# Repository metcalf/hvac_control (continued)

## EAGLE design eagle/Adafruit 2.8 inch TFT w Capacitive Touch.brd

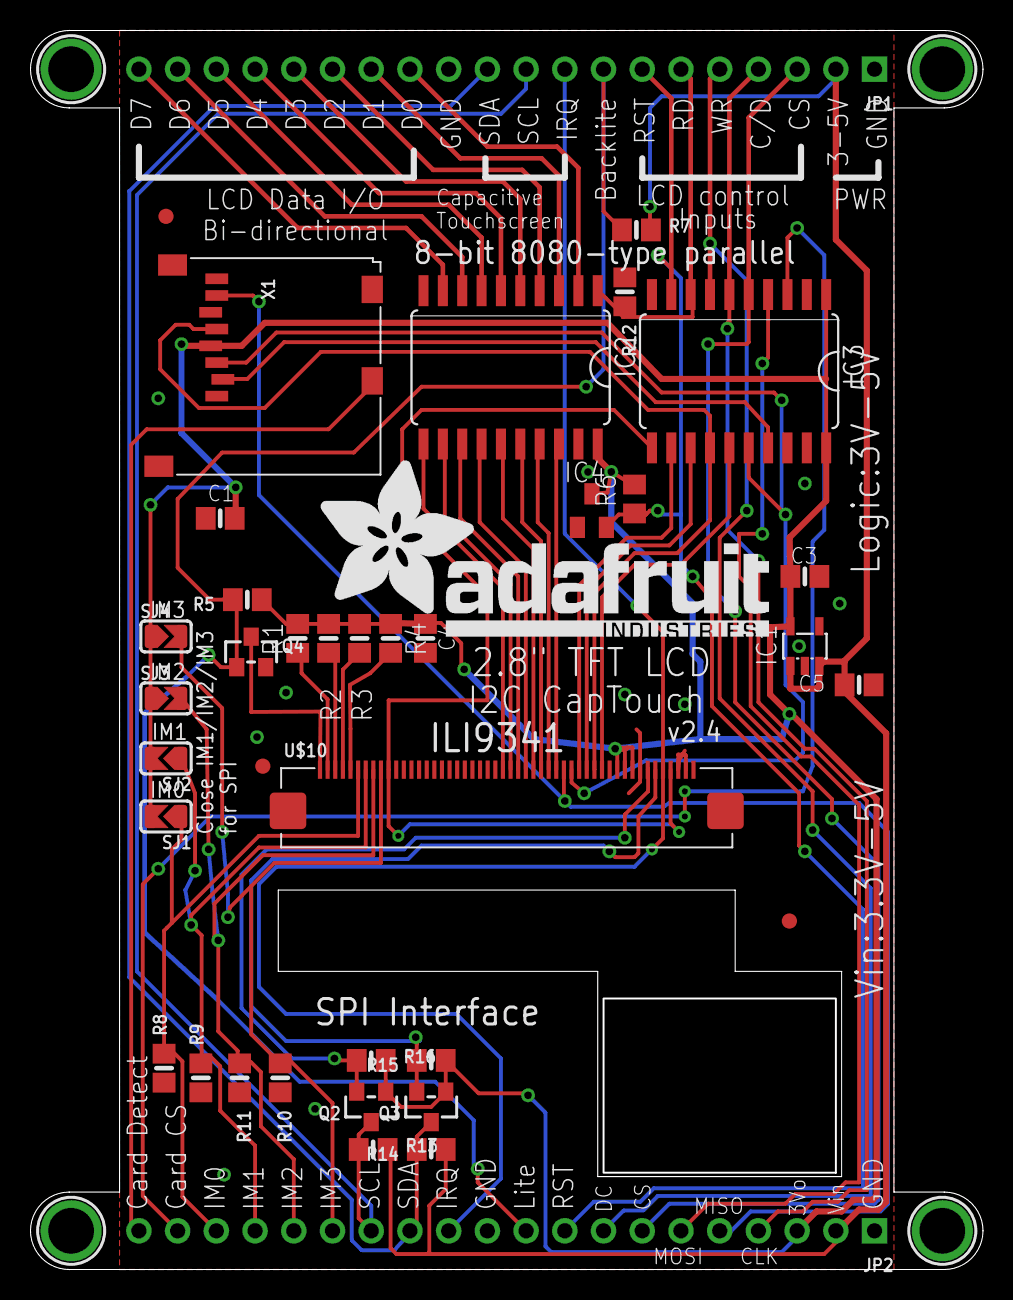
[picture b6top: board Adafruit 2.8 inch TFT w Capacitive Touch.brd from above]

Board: 2 copper layers, 62.5 x 81.3 mm, 43 parts (1 on the bottom side), 50 nets.

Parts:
C1, C3, C4, C5: 10uF; 0805-NO
IC1: MIC5225-3.3; SOT23-5L
IC2, IC3: 74LVC245; SO20W
IC4: APX803-SAG; SOT23
JP1, JP2: 1X20_ROUND
Q2, Q3, Q4: BSS138; SOT23-WIDE
R1, R2, R3, R4: 10; 0805-NO
R5: 2.2K; 0805-NO
R6: 10K; R0805
R7: 1K; 0805-NO
R8, R9, R10, R11, R12, R13, R14, R15, R16: 10K; 0805-NO
SJ1, SJ2, SJ3, SJ4: SOLDERJUMPER_ARROW_NOPASTE
U$7, U$15, U$16, U$17: MOUNTINGHOLE3.0THIN; MOUNTINGHOLE_3.0_PLATEDTHIN
U$9, U$11, U$23: FIDUCIAL; FIDUCIAL_1MM
U$10: 2.8" CTP ILI9341; TFT_2.83IN_240X320_50PIN
U$19: ADAFRUIT_TEXT_30MM
X1: microSD; MICROSD

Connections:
+5V: C5.1, IC1.1, IC1.3, JP1.2, JP2.2, R7.2, R13.2, R14.1
CARDDET: JP2.20, X1.CD2
CTP_IRQ: JP1.9, JP2.12, U$10.46
GND: C1.2, C3.2, C4.2, C5.2, IC1.2, IC2.10, IC2.19, IC3.10, IC3.19, IC4.1, JP1.1, JP1.12, JP2.1, JP2.11, Q4.2, R8.1, R9.1, R10.2, R11.2, R12.1, U$10.43, U$10.48, U$10.49, U$10.50, X1.6, X1.MT1, X1.MT2
IM0: JP2.18, R8.2, SJ1.1, U$10.6
IM1: JP2.17, R9.2, SJ2.1, U$10.7
IM2: JP2.16, R11.1, SJ3.2, U$10.8
IM3: JP2.15, R10.1, SJ4.2, U$10.9
LCD_CS: IC3.15, U$10.38
LCD_CS_5V: IC3.5, JP1.3, JP2.7
LCD_DATA0: IC2.18, U$10.32
LCD_DATA0_5V: IC2.2, JP1.13
LCD_DATA1: IC2.17, U$10.31
LCD_DATA1_5V: IC2.3, JP1.14
LCD_DATA2: IC2.16, U$10.30
LCD_DATA2_5V: IC2.4, JP1.15
LCD_DATA3: IC2.15, U$10.29
LCD_DATA3_5V: IC2.5, JP1.16
LCD_DATA4: IC2.14, U$10.28
LCD_DATA4_5V: IC2.6, JP1.17
LCD_DATA5: IC2.13, U$10.27
LCD_DATA5_5V: IC2.7, JP1.18
LCD_DATA6: IC2.12, U$10.26
LCD_DATA6_5V: IC2.8, JP1.19
LCD_DATA7: IC2.11, U$10.25
LCD_DATA7_5V: IC2.9, JP1.20
LCD_LITE: JP1.8, JP2.10, Q4.1, R5.2, R7.1
LCD_RD: IC3.12, U$10.35
LCD_RD_5V: IC2.1, IC3.8, JP1.6, R12.2
LCD_RS: IC3.14, U$10.37, X1.5
LCD_RST: IC3.11, U$10.10, U$10.47
LCD_RST_5V: IC3.9, IC4.2, JP1.7, JP2.9, R6.1
LCD_RS_5V: IC3.6, JP1.4, JP2.4
LCD_WR: IC3.13, U$10.36
LCD_WR_5V: IC3.7, JP1.5, JP2.8
unnamed: R4.2, U$10.5
unnamed: R1.2, U$10.2
unnamed: R2.2, U$10.3
unnamed: R3.2, U$10.4
unnamed: Q4.3, U$10.1
SCL_3V: Q2.2, R16.1, U$10.44
SCL_5V: JP1.10, JP2.14, Q2.3, R13.1
SDA_3V: Q3.2, R15.2, U$10.45
SDA_5V: JP1.11, JP2.13, Q3.3, R14.2
SDI_3V: IC3.16, U$10.34, X1.3
SDI_5V: IC3.4, JP2.6
SDO: JP2.5, U$10.33, X1.7
SD_CS_3V: IC3.17, X1.2
SD_CS_5V: IC3.3, JP2.19
VCC: C1.1, C3.1, C4.1, IC1.5, IC2.20, IC3.1, IC3.20, IC4.3, JP2.3, Q2.1, Q3.1, R1.1, R2.1, R3.1, R4.1, R5.1, R6.2, R15.1, R16.2, SJ1.2, SJ2.2, SJ3.1, SJ4.1, U$10.40, U$10.41, U$10.42, X1.4

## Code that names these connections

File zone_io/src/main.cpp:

#include <stdint.h>
#include <string.h>

#include <avr/interrupt.h>
#include <avr/io.h>
#include <avr/wdt.h>
#include <util/delay.h>

#define VLV_SW_CLK F_CLK_PER / 2
#define UART_BAUD 9600
#define SEND_INTERVAL_MS 450

struct Bits {
    unsigned b0 : 1, b1 : 1, b2 : 1, b3 : 1, b4 : 1, b5 : 1, b6 : 1, b7 : 1;
};
union BitByte {
    struct Bits bits;
    unsigned char byte;
};

volatile uint16_t vlv_sw_period_;

uint8_t port_states_[3];
volatile uint8_t tx_pos_;
BitByte tx_buffer_[3] = {(0x00 << 6), (0x01 << 6), (0x02 << 6)};

uint8_t getVlvState() {
    uint8_t vlv_sw_freq = VLV_SW_CLK / vlv_sw_period_;
    // NB: Rectified AC is double mains frequency (120hz)
    if (vlv_sw_freq < 30) {
        return 0; // Assume off
    } else if (vlv_sw_freq < 90) {
        return 1; // Assume one channel on (~60hz)
    } else {
        return 2; // Assume both channels on (~120hz)
    }
}

void setupUSART() {
    VPORTA.DIR |= PIN1_bm; // TxD on PA1
    USART1.CTRLA = USART_DREIE_bm;
    USART1.CTRLB = USART_TXEN_bm; // TX only
    USART1.BAUD = (uint16_t)((float)(F_CLK_PER * 64 / (16 * (float)UART_BAUD)) + 0.5);
    // Configure async 8N1 (this is the default anyway, being explicit for clarity)
    USART1.CTRLC = USART_CMODE_ASYNCHRONOUS_gc | USART_PMODE_DISABLED_gc | USART_SBMODE_1BIT_gc |
                   USART_CHSIZE_8BIT_gc;
}

void txNext() {
    USART1_TXDATAL = tx_buffer_[tx_pos_].byte;
    tx_pos_ = (tx_pos_ + 1) % sizeof(tx_buffer_);
}

void startTx() {
    if (tx_pos_ != 0 || (USART1.STATUS & USART_DREIF_bm)) {
        return; // We're still writing, skip this Tx
    }

    BitByte vlv_state = {.byte = getVlvState()};

    tx_buffer_[0] = {.bits = {.b0 = VPORTA.IN & PIN2_bm, // FC1_V
                              .b1 = VPORTA.IN & PIN3_bm, // FC1_OB
                              .b2 = VPORTA.IN & PIN4_bm, // FC2_V
                              .b3 = VPORTA.IN & PIN5_bm, // FC2_OB
                              .b4 = VPORTA.IN & PIN6_bm, // FC3_V
                              .b5 = VPORTA.IN & PIN7_bm, // FC3_OB
                              .b6 = 0,
                              .b7 = 0}};
    tx_buffer_[1] = {.bits = {.b0 = VPORTB.IN & PIN5_bm, // FC4_V
                              .b1 = VPORTB.IN & PIN4_bm, // FC4_OB
                              .b2 = VPORTB.IN & PIN1_bm, // TS1_W
                              .b3 = VPORTB.IN & PIN2_bm, // TS1_Y
                              .b4 = VPORTB.IN & PIN3_bm, // TS2_W
                              .b5 = VPORTB.IN & PIN0_bm, // TS2_Y
                              .b6 = 1,
                              .b7 = 0}};
    tx_buffer_[2] = {.bits = {.b0 = VPORTC.IN & PIN1_bm, // TS3_W
                              .b1 = VPORTC.IN & PIN2_bm, // TS3_Y
                              .b2 = VPORTC.IN & PIN3_bm, // TS4_W
                              .b3 = 0,                   // TS4_Y (not connected)
                              .b4 = vlv_state.bits.b0,
                              .b5 = vlv_state.bits.b1,
                              .b6 = 0,
                              .b7 = 1}};

    txNext();
}

void setupPins() {
    PORTA.PIN2CTRL |= PORT_PULLUPEN_bm; // FC1_V
    PORTA.PIN3CTRL |= PORT_PULLUPEN_bm; // FC1_OB
    PORTA.PIN4CTRL |= PORT_PULLUPEN_bm; // FC2_V
    PORTA.PIN5CTRL |= PORT_PULLUPEN_bm; // FC2_OB
    PORTA.PIN6CTRL |= PORT_PULLUPEN_bm; // FC3_V
    PORTA.PIN7CTRL |= PORT_PULLUPEN_bm; // FC3_OB
    PORTB.PIN1CTRL |= PORT_PULLUPEN_bm; // TS1_W
    PORTB.PIN2CTRL |= PORT_PULLUPEN_bm; // TS1_Y
    PORTB.PIN3CTRL |= PORT_PULLUPEN_bm; // TS2_W
    PORTB.PIN5CTRL |= PORT_PULLUPEN_bm; // FC4_V
    PORTB.PIN4CTRL |= PORT_PULLUPEN_bm; // FC4_OB
    PORTB.PIN0CTRL |= PORT_PULLUPEN_bm; // TS2_Y
    PORTC.PIN0CTRL |= PORT_PULLUPEN_bm; // TS3_W
    PORTC.PIN1CTRL |= PORT_PULLUPEN_bm; // TS3_W
    PORTC.PIN2CTRL |= PORT_PULLUPEN_bm; // TS3_Y
}

void setupVlvTimer() {
    // Configure TCB0 on WO0/PC0 for frequency measurement for VLV_SW_IO
    PORTMUX.TCBROUTEA = PORTMUX_TCB0_ALT1_gc;
    TCB0.CTRLB = TCB_CNTMODE_FRQ_gc; // Frequency count mode
    //TCB0.EVCTRL = TCB_CAPTEI_bm; // I had this set originally but think it isn't necessary?
    TCB0.INTCTRL = TCB_CAPT_bm;
    TCB0.CTRLA =
        (TCB_ENABLE_bm | TCB_CLKSEL_DIV2_gc); // Configure tach frequency measurement @ ~156khz
}

int main(void) {
    wdt_enable(WDTO_1S);

    CLKCTRL.MCLKCTRLB = CLKCTRL_PEN_bm | CLKCTRL_PDIV_64X_gc; // Divide main clock by 64 = 312500hz

    setupUSART();
    setupPins();
    setupVlvTimer();

    while (1) {
        wdt_reset();

        // Poll pin states every 833us for 50ms. This gives us a sample rate
        // of 1200hz on a 120hz signal for 6 cycles
        memset(port_states_, 0, sizeof(port_states_));
        for (int i = 0; i < 60; i++) {
            // Exclude PA0(UDPI) and PA1(UART)
            port_states_[0] |= VPORTA.IN & ~(PIN0_bm | PIN1_bm);
            port_states_[1] |= VPORTB.IN;
            // Exclude PC0 (VLV_SW)
            port_states_[2] |= VPORTC.IN & ~(PIN0_bm);

            _delay_us(833);
        }

        startTx();

        // Delay while sending since we don't need the data very frequently
        wdt_reset();
        _delay_ms(SEND_INTERVAL_MS);
    }
}

ISR(TCB0_INT_vect) {
    if (TCB0.INTFLAGS & TCB_OVF_bm) {
        // If we overflowed, clear the overflow bit and set an invalid period
        TCB0.INTFLAGS &= ~TCB_OVF_bm;
        vlv_sw_period_ = 0;
    } else {
        vlv_sw_period_ = TCB0.CCMP; // reading CCMP clears interrupt flag
    }
}

ISR(USART1_DRE_vect) {
    if (tx_pos_ == 0) {
        return; // Nothing to write right now
    }

    txNext();
}

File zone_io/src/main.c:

#include <stdint.h>
#include <string.h>

#include "avr/interrupt.h"
#include "avr/io.h"
#include "avr/wdt.h"
#include "util/atomic.h"
#include "util/delay.h"

#define VLV_SW_CLK F_CLK_PER / 2
#define UART_BAUD 9600
#define SEND_INTERVAL_MS 450

// Poll 200 times at 1200hz. Gives us 20 full cycles of data and takes ~167ms
// Our read strategy is designed to filter out external noise at the optoisolator inputs.
// The Taco valves in particular throw off a lot of noise and cause pins to flicker.
#define N_SAMPLES 200
// The optoisolators are pretty sensitive so it should read high
// most of the time if the pin is high. The internal pull-ups is very weak (~35kohm)
// so a tiny amount of current (<0.1mA) should pull the pin high. This corresponds to
// something like 0.2mA at the opto input which requires 5-6V.
#define INPUT_THRESHOLD (N_SAMPLES / 4)
// We can set a very low threshold for the one channel state since there should be
// *nothing* on the pin when no channels are on. This also helps avoid rapid switching
// of the pump if the controller thinks the only active channel is rapidly turning on and off.
// We're stuck using a somewhat higher threshold for the both channels state since it has
// to be larger than half the total samples or we could falsely trigger it when only one channel is on.
#define ONE_VALVE_THRESHOLD (N_SAMPLES / 8)
#define BOTH_VALVE_THRESHOLD (uint8_t)(N_SAMPLES * 0.53)

volatile uint16_t vlv12_sw_period_, vlv34_sw_period_;
volatile uint8_t port_read_flag_;
volatile uint8_t port_in_values_[3];
volatile uint8_t *ports_[] = {&VPORTA.IN, &VPORTB.IN, &VPORTC.IN};

volatile uint8_t tx_pos_;
char tx_buffer_[3];

const uint8_t tx_map_[3][6] = {
    {
        // PORTA
        PIN2_bm, // FC1_V
        PIN3_bm, // FC1_OBpwm
        PIN4_bm, // FC2_V
        PIN5_bm, // FC2_OB
        PIN6_bm, // FC3_V
        PIN7_bm, // FC3_OB
    },
    {
        // PORTB
        PIN5_bm, // FC4_V
        PIN4_bm, // FC4_OB
        PIN1_bm, // TS1_W
        PIN2_bm, // TS1_Y
        PIN3_bm, // TS2_W
        PIN0_bm, // TS2_Y
    },
    {
        // PORTC
        PIN0_bm, // TS3_W
        PIN1_bm, // TS4_W
    },
};

void setupUSART() {
    VPORTA.DIR |= PIN1_bm; // TxD on PA1
    // Configure async 8N1 (this is the default anyway, being explicit for clarity)
    USART1.CTRLC = USART_CMODE_ASYNCHRONOUS_gc | USART_PMODE_DISABLED_gc | USART_SBMODE_1BIT_gc |
                   USART_CHSIZE_8BIT_gc;
    USART1.BAUD = (uint16_t)((double)(F_CLK_PER * 64 / (16 * (double)UART_BAUD)) + 0.5);
    USART1.CTRLB = USART_TXEN_bm; // TX only
}

void startTx(uint8_t *port_states, uint8_t vlv12_state, uint8_t vlv34_state) {
    if (USART1.CTRLA & USART_DREIE_bm) {
        return; // We're still writing, skip this Tx
    }

    for (int i = 0; i < 3; i++) {
        int lim = i < 2 ? 6 : 2;
        tx_buffer_[i] = i << 6; // Set payload ID in last 2 bits
        for (int j = 0; j < lim; j++) {
            if (port_states[i] & tx_map_[i][j]) {
                tx_buffer_[i] |= (0x01 << j);
            }
        }
    }

    tx_buffer_[2] |= (vlv12_state << 2) | (vlv34_state << 4);

    USART1.CTRLA |= USART_DREIE_bm;
}

void setupInputPins() {
    VPORTA.DIR = 0;
    VPORTB.DIR = 0;
    VPORTC.DIR = 0;

    register8_t *pins[] = {
        &PORTA.PIN2CTRL, &PORTA.PIN3CTRL, &PORTA.PIN4CTRL, &PORTA.PIN5CTRL,
        &PORTA.PIN6CTRL, &PORTA.PIN7CTRL,

        &PORTB.PIN0CTRL, &PORTB.PIN1CTRL, &PORTB.PIN2CTRL, &PORTB.PIN3CTRL,
        &PORTB.PIN4CTRL, &PORTB.PIN5CTRL,

        &PORTC.PIN0CTRL, &PORTC.PIN1CTRL, &PORTC.PIN2CTRL, &PORTC.PIN3CTRL,
    };

    for (int i = 0; i < (sizeof(pins) / sizeof(pins[0])); i++) {
        // Enable pullups on all input pins and invert inputs since NPN optos pull down
        *pins[i] = (PORT_PULLUPEN_bm | PORT_INVEN_bm);
    }
}

void setupPinCheckTimer() {
    // Sample at 1200hz (10x rectified mains frequency)
    TCA0.SINGLE.PER = (F_CLK_PER + 600) / 1200;
    TCA0.SINGLE.INTCTRL = TCA_SINGLE_OVF_bm;
    TCA0.SINGLE.CTRLA = TCA_SINGLE_CLKSEL_DIV1_gc;
}

int main(void) {
    wdt_enable(0x8); // 1 second (note the constants in avr/wdt are wrong for this chip)

    CPU_CCP = CCP_IOREG_gc; /* Enable writing to protected register MCLKCTRLB */
    CLKCTRL.MCLKCTRLB = CLKCTRL_PEN_bm | CLKCTRL_PDIV_16X_gc; // Divide main clock by 16 = 1.25mhz

    setupInputPins();
    setupUSART();
    setupPinCheckTimer();

    sei(); // Enable interrupts

    while (1) {
        wdt_reset();

        uint8_t port_counts[3][8] = {};

        port_read_flag_ = 0;
        TCA0.SINGLE.INTFLAGS |= TCA_SINGLE_OVF_bm; // Clear interrupt flag
        TCA0.SINGLE.CNT = 0;                       // Start at zero
        TCA0.SINGLE.CTRLA |= TCA_SINGLE_ENABLE_bm; // Start the timer

        for (int i = 0; i < N_SAMPLES; i++) {
            while (1) {
                uint8_t read;
                ATOMIC_BLOCK(ATOMIC_FORCEON) { read = port_read_flag_; }
                if (read) {
                    break;
                }
            }

            for (uint8_t port_idx = 0; port_idx < 3; port_idx++) {
                for (uint8_t pin = 0; pin < 8; pin++) {
                    if (port_in_values_[port_idx] & (1 << pin)) {
                        port_counts[port_idx][pin]++;
                    }
                }
            }
            ATOMIC_BLOCK(ATOMIC_FORCEON) { port_read_flag_ = 0; }
        }

        TCA0.SINGLE.CTRLA &= ~TCA_SINGLE_ENABLE_bm; // Stop the timer

        uint8_t port_states[3] = {0};

        for (uint8_t port_idx = 0; port_idx < 3; port_idx++) {
            for (uint8_t pin = 0; pin < 8; pin++) {

                if (port_counts[port_idx][pin] > INPUT_THRESHOLD) {
                    port_states[port_idx] |= (1 << pin);
                }
            }
        }

        uint8_t vlv_states[2] = {0};
        for (int i = 0; i < 2; i++) {
            // PC2 and PC3 are used for VLV1/2 and VLV3/4 respectively
            uint8_t count = port_counts[2][i + 2];

            if (count > BOTH_VALVE_THRESHOLD) {
                vlv_states[i] = 2; // Both channels on
            } else if (count > ONE_VALVE_THRESHOLD) {
                vlv_states[i] = 1; // One channel on
            } else {
                vlv_states[i] = 0; // Off
            }
        }

        startTx(port_states, vlv_states[0], vlv_states[1]);

        // Delay while sending since we don't need the data very frequently
        wdt_reset();
        _delay_ms(SEND_INTERVAL_MS);
    }
}

ISR(TCA0_OVF_vect) {
    if (port_read_flag_ == 0) {
        for (int i = 0; i < 3; i++) {
            port_in_values_[i] = *ports_[i];
        }
        port_read_flag_ = 1;
    }

    TCA0.SINGLE.INTFLAGS |= TCA_SINGLE_OVF_bm; // Clear interrupt flag
}

ISR(USART1_DRE_vect) {
    USART1_TXDATAL = tx_buffer_[tx_pos_];
    tx_pos_ = (tx_pos_ + 1) % sizeof(tx_buffer_);

    if (tx_pos_ == 0) {
        // Write complete, disable interrupt
        USART1.CTRLA &= ~USART_DREIE_bm;
    }
}

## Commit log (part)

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2024-02-03 Upgrade to esp-idf 5.x
2024-02-06 controller compiles
2024-02-07 wip controller with ui
2024-02-07 move ControllerApp to library
2024-02-07 Refactor ControllerApp to remove uc deps
2024-02-08 got a running test
2024-02-08 Status logging and testing
2024-02-09 Wifi and tests et al
2024-02-20 Fix hardware interfaces, mem allocation, points
2024-02-21 wrap lv_ access in mutex
2024-02-21 lvgl work
2024-02-21 don't track sdkconfig backups
2024-02-21 Faster rtos tick and don't use CS
2024-02-21 Change sdkconfig for perf
2024-02-22 wip loggers
2024-02-22 squareline
2024-02-22 mostly working ui
2024-02-22 Properly init schedule time rollers
2024-02-24 working fancoil/makeup+tester
2024-02-24 wip settings screens
2024-02-24 WIP settings
2024-02-24 WIP synced temp rollers
2024-02-26 More UI work and tests
2024-02-28 more controller wip
2024-02-29 WIP new sensor implementation
2024-02-29 Import rx8111 RTC linux driver verbatim
2024-02-29 Add clock on homescreen
2024-03-01 New config architecture, co2 calibration, some UI improvements
2024-03-04 Add support for 2nd valve sw input pin
2024-03-18 Moar tests
2024-03-23 Fix sleep wake
2024-03-23 some co2 calibration tweaks
2024-03-25 Tests and fixes for co2 calibration
2024-03-25 Include hardware files
2024-03-25 Remove old eagle files now that we have git history
2024-03-27 RTC and CO2 cal debugging
2024-03-28 Initial zone controller UI
2024-03-28 Initial zone controller UI with shared code extracted
2024-03-28 Copy configs from controller
2024-03-28 Compiling with UI
2024-03-29 compiles
2024-03-29 Maybe working test mode
2024-03-29 WIP zone controller tests
2024-04-04 move mutexes out of MessageManager and into *UIManager
2024-04-06 more testing and fixing
2024-04-06 more tests and todos
2024-04-12 Remove 'Force AC' to simplify broken logic
2024-04-14 Finish removing secondary controller and write more tests
2024-06-24 latest boards and cases
2024-07-08 update boards and labeling
2024-07-10 Bump UI
2024-07-10 Initial pid simulator
2024-07-12 hvac.System
2024-07-12 simple fan cooling
2024-07-17 more wip simulator
2024-07-18 wip integration wrong
2024-07-19 pretty reasonable model
2024-07-27 bit of simulator cleanup
2024-08-22 start work on CXI modbus client
2024-08-22 initial fancoil_tester
2024-08-22 rando
2024-08-24 More work on cxi
2024-08-24 WIP weather fetching
2024-08-26 Add fancoil modbus logic to controller
2024-08-31 first pass at weather client
2024-09-01 WIP separate broan code
2024-09-02 working broan code
2024-09-02 Bump the clock on the S&P code too so we don't hit modbus timeouts as much
2024-09-02 Move shared code for the fresh air clients to a shared lib
2024-09-04 Run AC if coil is already cold
2024-09-09 fresh air control updates
2024-09-10 Simplify PID simulation code
2024-09-11 Split out simulation PIDComponent
2024-09-17 more pid algo simplification
2024-09-17 mostly working demand-based modulo linker issues
2024-09-17 move to right place
2024-09-18 linear implementation with demands
2024-09-18 WIP tests
2024-09-19 tests compile
2024-09-20 passing tests
2024-09-21 PID passes tests
2024-09-22 constrain iDemand further to avoid windup
2024-09-29 todo
2024-09-29 wip release script
2024-10-02 make wifi an IDF component and start work on OTA
2024-10-02 compiling OTA client
2024-11-15 No DHW
2024-11-16 WIP switch to pulling weather from home assistant
2024-11-16 compiling with home assistant client
2024-11-17 Remote logging compiles
2024-11-17 bug fixes
2024-11-17 More minor fixes/improvements
2024-11-21 WIP updates and bug fixes
2024-11-21 working HASS client, temporary retreat on remote logging
2024-11-22 working remote logger, some fixes
2024-11-22 memory
2024-11-23 wifi reconnection, lower stack usage in remote_logger
2024-11-25 Fixed crash on formatting issue
2024-11-26 start moving things from shared_libs to components
2024-11-26 Finish moves from shared_libs to components
2024-11-26 WIP migrate controller to ESP IDF
2024-11-26 more WIP migrate to ESP IDF
2024-11-27 Working local unit tests
2024-11-27 cleanup ESP IDF bits
2024-11-30 NetworkTaskManager; Mostly working HVAC switching limits, failing tests
2024-11-30 Fix tests
2024-12-09 Use sdkconfig.defaults for better config management (controller)
2024-12-09 correctly set ESP IDF monitor defaults
2024-12-09 Some cleanup from the ESP IDF move
2024-12-09 Share log_heap_stats
2024-12-09 Update release.sh for ESP IDF
2024-12-09 more NTM
2024-12-09 UI tweaks and rearrange UI folder
2024-12-09 Fix messages
2024-12-09 tweak default name
2024-12-09 zc fixes
2024-12-10 minor zc fixes
2024-12-10 Reduce log level
2024-12-21 zone_controller ota mark valid
2025-06-11 mostly controller bug and test fixes
2025-06-12 few ui bug fixes
2025-06-13 system power and fresh air ID bugs
2025-06-13 do not allow cancelling precooling until we make the ui better
2025-06-13 Add a test main method to properly read gmock command line args
2025-07-08 spaces instead of tabs in logs
2025-07-09 Fix changing equipment config
2025-07-09 Change how algos are initialized
2025-07-09 Add turn on hysteresis to fan
2025-07-09 Tweak parameters to reduce short cycling more
2025-07-09 adjust for outdoor temp, log fancoil state, integral deadband
2025-07-10 fix bug in windup deadzone
2025-07-10 debug pid
2025-07-10 Tune fan parameters a bit more
2025-07-10 Provide more reasonable tuning for fancoils
2025-07-10 Better logging of state
2025-07-10 fix bug preventing OTA
2025-07-10 try to talk to real heatpump
2025-07-12 use std::size other places to reduce risk of bugs
2025-07-12 System On label
2025-07-12 I think this could hide a bug
2025-07-12 start swapping A/B pins
2025-07-12 Fix IncreasesFanSpeedOverTime and Precooling tests for new parameters
2025-07-12 Implement canceling HVAC change limit
2025-07-12 Put the restart button label on the button
2025-07-13 Bump up makeup air speed
2025-07-16 switch modbus TXD pin and add some logging
2025-07-16 Revert "Update esp-modbus to v1.0.18"
    This version introduces some breaking changes by paying attention to the param_type and
    param_size for the descriptors which I have been setting to zero.
    This reverts commit 6b57b70cb332cc7453fbac6a019fac561a86f53f.
2025-07-16 more logging improvements
2025-07-16 Fix inverted fancoil O/B
2025-07-17 Fix clang-format inheritance
2025-07-17 CXI fancoil debugging
2025-07-17 Don't query fancoil if not used
2025-07-17 log coil temps
2025-07-17 more fancoil debug logging
2025-07-17 correct comments on timers in fresh_air_control
2025-07-17 enable overflow interrupt
2025-07-17 Retry all CXI modbus commands with backoff
2025-07-18 Bit higher threshold for activating AC
2025-07-18 use weather data instead of polling fresh air unit
2025-07-18 Fix display of outdoor temp and allow older temps
2025-07-19 Fix tests for switch to weather API
2025-07-19 Fix precooling messaging and make precooling more aggressive
2025-07-22 Reasons to enumbs
2025-07-22 Log on fan/hvac state changes
2025-07-24 extend precooling
2025-07-24 Don't use A/C with cool outdoor temps
2025-07-24 Rewrite zone_io to reduce sensitivity to electrical noise
2025-07-24 ignore eagle backup files
2025-07-24 WIP debugging new zone_io code
2025-07-24 Working new zone_io and fix some tests
2025-07-24 Do not turn zone pump on until at least one valve is open
2025-09-17 Fix release to use sudo
2025-09-23 Fix test thresholds from 4850289e
2025-09-23 Turn on A/C when outdoor temp exceeds a threshold
2025-09-23 Make various ControllerApp constants public to improve tests
2025-09-30 Switch to https for homeassistant
2025-09-30 Make pressure formatting portable
2025-09-30 reformat ESPOTAClient
2025-09-30 Send temperature correction to SCD40
2025-10-01 Report AQI instead of humidity
2025-10-09 adjust temp offset a bit
2025-10-11 Fix deadlock turning on and off
2025-10-15 tap message to scroll
2025-10-27 temperature sensor board for controllers
2025-10-29 Don't mess with heat pump in test mode
2025-10-29 save temp_board as printed
2025-10-30 get rid of apparently unused 'getValve'
2025-10-30 fix logging bug
2025-10-30 Refactor out ZCApp
2025-10-30 Remove dependencies for testability
2025-10-30 Create AbstractZCUIManager for testability
2025-10-30 Get existing tests working again
2025-10-31 logging comment
2025-10-31 Really fix logging this time
2025-10-31 Rate limit state change on valves/pumps
2025-10-31 Better debouncing on zone_io
2025-10-31 Reduce repetitive logging during rate limiting
2025-10-31 Move UI files to export folder
2025-10-31 Show version in settings
2025-10-31 Move zone_io constants to defines so I don't forget any
2025-10-31 Hide settings panel by default (fixes 32e94a3561)
2025-10-31 clear TSConflictingCallsError automatically
2025-11-10 tweak AC parameters
2025-11-10 Initial Claude Code config
2025-11-10 Make STS sensor i2c address a parameter
2025-11-10 Fix tests from 98add5d
2025-11-10 Refactor temp offset code
2025-11-10 update submodule
2025-11-10 Formatting and compilation fixes
2025-11-10 Reference tempC when checking if sensors are ready
2025-11-10 Improve logging and add tests around HVAC change limits
2025-11-10 off-board temp pcb tester
2025-11-11 Fix minor bugs in offboard sensor
2025-11-11 Fix AC without outdoor temp reading
2025-11-11 Calibrate off-board temp sensors
2025-11-12 Fix bug in fan override message
2025-11-12 Fix bug in sensor init
2025-11-12 Use const more for safety
2025-11-12 Add outputActive to PID instead of integral deadband
2025-11-12 WIP parse_logs
2025-11-12 Update parse_logs and add fetch_logs
2025-11-12 Finish parse_logs
2025-11-18 Adjust sensor offset a bit
2025-11-18 Don't show precooling msg when below cool setpoint
2025-11-18 Tweak fancoil thresholds
2025-11-18 Emit parsed logs to stdout
2025-11-18 Implement load control for powerwall
2025-11-19 parse_logs: include derived columns
2025-11-19 Adjust tests for tweaked fancoil thresholds
2025-11-19 Different fancoil setpoints for PBR
2025-11-29 Mqtt home client wip
2025-11-29 more wip
2025-11-29 Switch to MqttHomeClient and rm http-based HASSClient
2025-11-29 switch topics
2025-11-29 mqtt fixes
2025-12-02 enable load shedding from powerwall
2025-12-03 WIP homeassistant climate mqtt
2025-12-03 WIP HA climate mqtt
2025-12-03 working MQTT climate
2025-12-10 Working MQTT climate commands
2025-12-10 WIP continuous fan UI, config, config migrations
2025-12-10 Continuous fan option
2025-12-11 Stop continuous venting at night when it's colder.
2025-12-11 WIP exhaust ctrl
2025-12-11 exhaust control modbus implementation
2025-12-11 exhaust control handling
2025-12-12 fixes, getCO2Offset
2025-12-13 run exhaust for 20m
2025-12-19 add input debounce on exhaust control
2025-12-27 fix pin inversion for exhaust ctrl
2025-12-27 fix exhaust ctrl timing
2026-02-28 Tweak fan cooling parameters
2026-02-28 Implement fan min on time
2026-03-18 Precooling with high outdoor temps
2026-03-19 poll heat pump current and ambient temp
2026-03-19 WIP implement MQTT home assistant communication for zone controller
2026-03-19 Remove CO2 calibration arbitrary ppm threshold
2026-03-19 Bump CO2 baseline while we're here
2026-06-07 set hostname
2026-06-07 always set hostname on init
2026-06-07 Add backoff on wifi retries
2026-06-07 WIP connectivity watchdog
2026-06-07 Check firmware version output is correct
2026-06-07 connectivity watchdog using ota endpoint
2026-06-08 controller .clangd
2026-06-08 Shorter restart interval on network issues
2026-06-08 Use s_mutex for consistency
2026-06-09 continue zone controller MQTT implementation
2026-06-09 wip publish more zone controller data
2026-06-10 Name zone controller over mqtt
2026-06-10 Set AQI color based on value
2026-06-10 Avoid losing remote logger messages when disconnected
2026-06-10 Add a logw line on restart
2026-06-17 AC on/off thresholds relative to cooling setpoint
2026-06-17 Do not rate limit IO state changes in test mode
2026-06-17 Fix rate limiting IOs on startup
